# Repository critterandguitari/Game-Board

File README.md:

Game-Board
==========

A add-on board to the Video Critter HiRes.  It has buttons and a USB port for proramming the Video Critter HiRes from computer.

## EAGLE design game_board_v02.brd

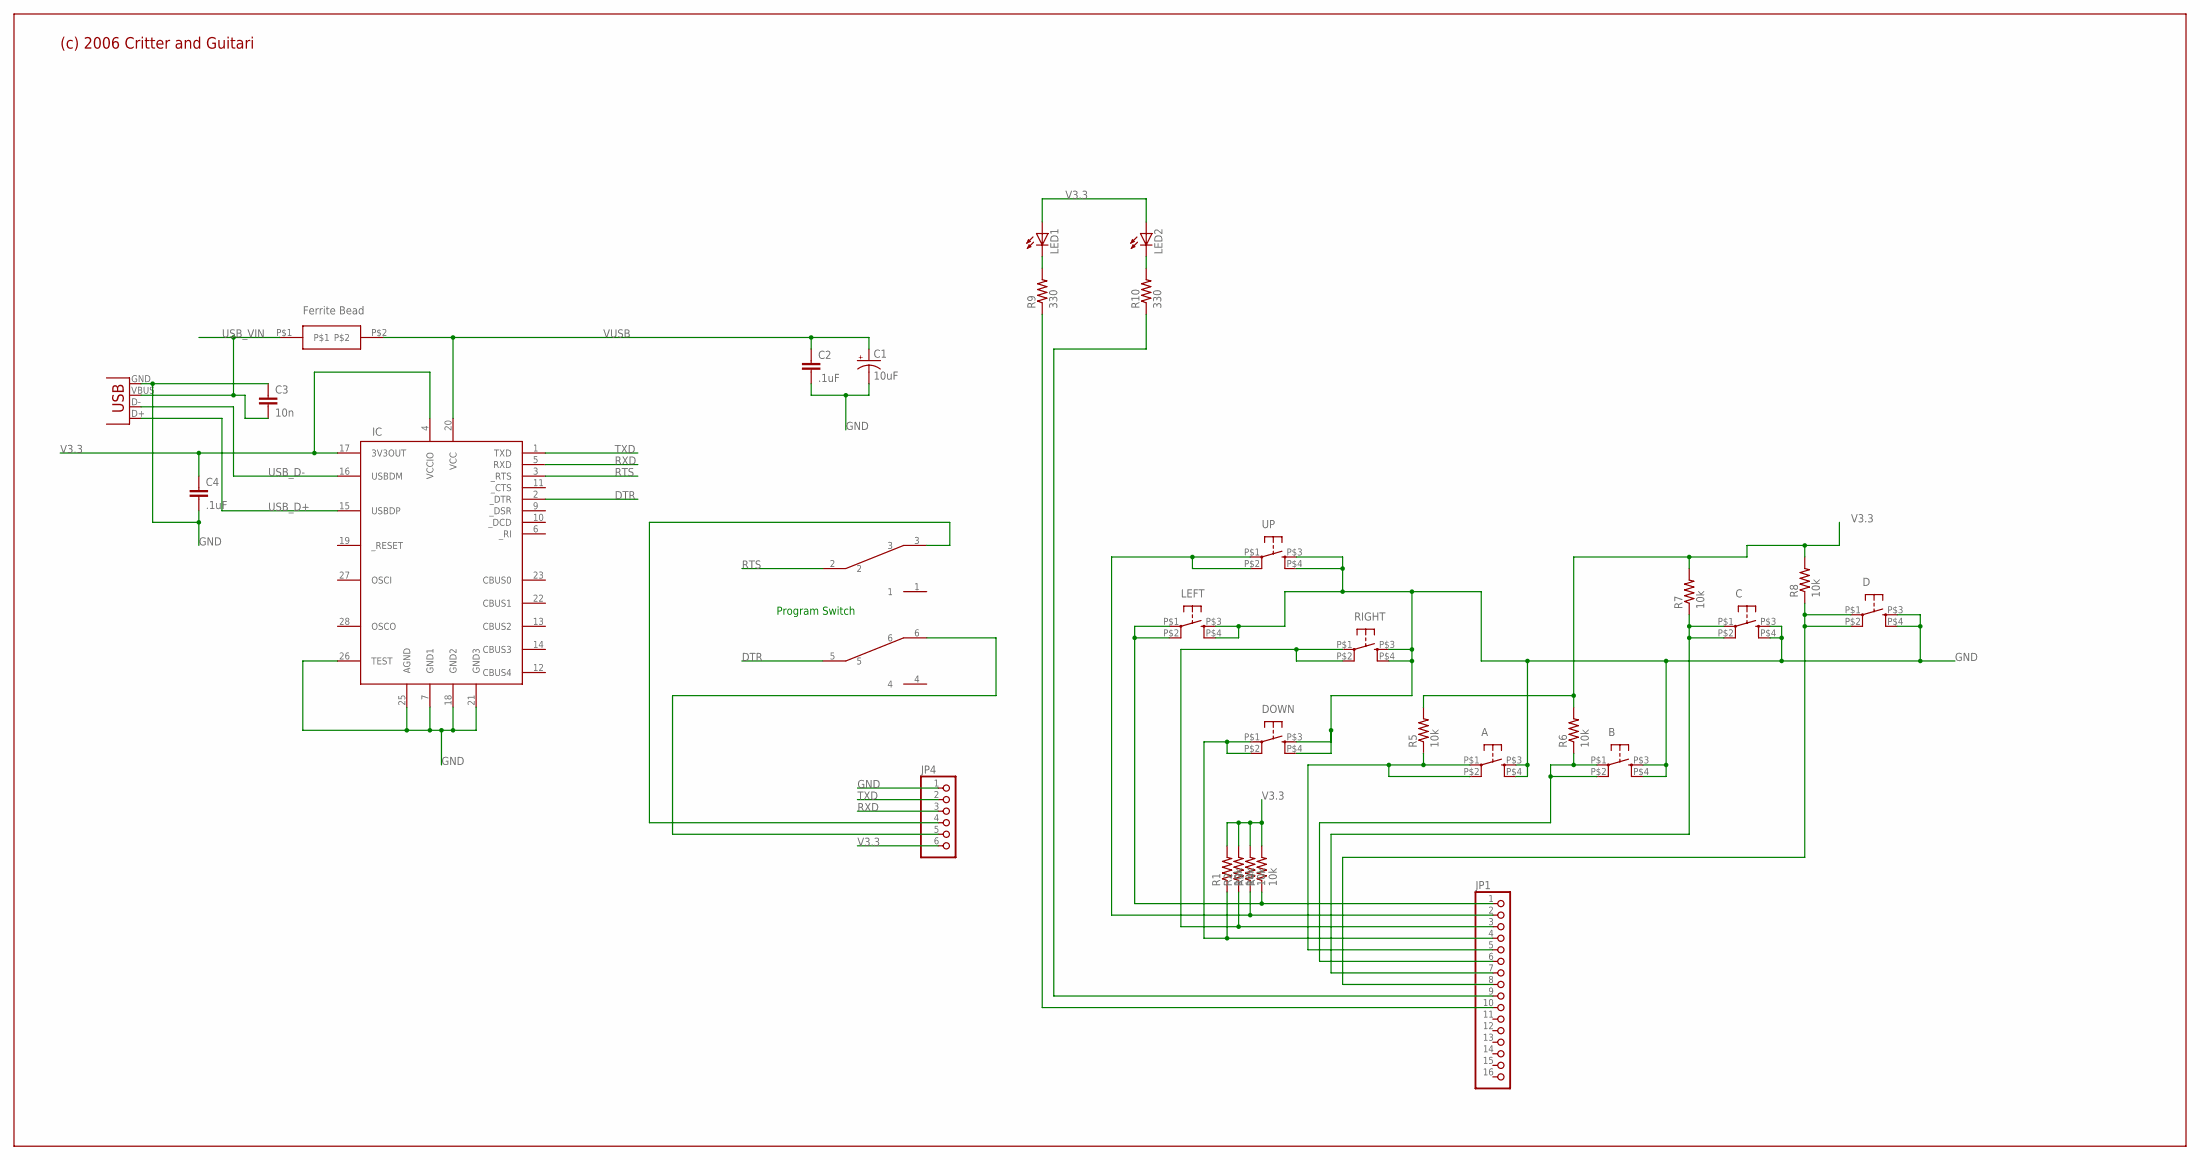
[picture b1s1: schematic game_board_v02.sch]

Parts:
A: TAC_SWITCHKSA_SEALED_TAC_SWITCH; KSA_SEALED_TAC_SWITCH
B: TAC_SWITCHKSA_SEALED_TAC_SWITCH; KSA_SEALED_TAC_SWITCH
C: TAC_SWITCHKSA_SEALED_TAC_SWITCH; KSA_SEALED_TAC_SWITCH
C1: 10uF; CPOL_1206
C2, C4: .1uF; C0603
C3: 10n; C0603
D: TAC_SWITCHKSA_SEALED_TAC_SWITCH; KSA_SEALED_TAC_SWITCH
DOWN: TAC_SWITCHKSA_SEALED_TAC_SWITCH; KSA_SEALED_TAC_SWITCH
IC: FT232RL; SSOP28DB
JP1: PINHD-1X16; 1X16
JP4: PINHD-1X6; 1X06
LED1, LED2: LED1206; CHIPLED_1206
LEFT: TAC_SWITCHKSA_SEALED_TAC_SWITCH; KSA_SEALED_TAC_SWITCH
R1, R2, R3, R4, R5, R6, R7, R8: 10k; R0603
R9, R10: 330; R0603
RIGHT: TAC_SWITCHKSA_SEALED_TAC_SWITCH; KSA_SEALED_TAC_SWITCH
U$1: FERRITE_BEAD
U$2: SWITCH_DPDT; SWITCH_DPDT_SMT
UP: TAC_SWITCHKSA_SEALED_TAC_SWITCH; KSA_SEALED_TAC_SWITCH
X2: USB-B-H

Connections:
DTR: IC.2 (_DTR), U$2.5
GND: A.P$3 (S), A.P$4 (S1), B.P$3 (S), B.P$4 (S1), C.P$3 (S), C.P$4 (S1), C1.C (-), C2.2, C3.1, C4.2, D.P$3 (S), D.P$4 (S1), DOWN.P$3 (S), DOWN.P$4 (S1), IC.7 (GND1), IC.18 (GND2), IC.21 (GND3), IC.25 (AGND), IC.26 (TEST), JP4.1, LEFT.P$3 (S), LEFT.P$4 (S1), RIGHT.P$3 (S), RIGHT.P$4 (S1), UP.P$3 (S), UP.P$4 (S1), X2.GND
unnamed: JP4.4, U$2.3
unnamed: JP4.5, U$2.6
unnamed: JP1.1, LEFT.P$1, LEFT.P$2 (P1), R4.1
unnamed: JP1.2, R3.1, UP.P$1, UP.P$2 (P1)
unnamed: JP1.3, R2.1, RIGHT.P$1, RIGHT.P$2 (P1)
unnamed: DOWN.P$1, DOWN.P$2 (P1), JP1.4, R1.1
unnamed: A.P$1, A.P$2 (P1), JP1.5, R5.1
unnamed: B.P$1, B.P$2 (P1), JP1.6, R6.1
unnamed: C.P$1, C.P$2 (P1), JP1.7, R7.1
unnamed: D.P$1, D.P$2 (P1), JP1.8, R8.1
unnamed: LED1.C, R9.2
unnamed: LED2.C, R10.2
unnamed: JP1.10, R9.1
unnamed: JP1.9, R10.1
RTS: IC.3 (_RTS), U$2.2
RXD: IC.5 (RXD), JP4.3
TXD: IC.1 (TXD), JP4.2
USB_D+: IC.15 (USBDP), X2.D+
USB_D-: IC.16 (USBDM), X2.D-
USB_VIN: C3.2, U$1.P$1, X2.VBUS
V3.3: C4.1, IC.4 (VCCIO), IC.17 (3V3OUT), JP4.6, LED1.A, LED2.A, R1.2, R2.2, R3.2, R4.2, R5.2, R6.2, R7.2, R8.2
VUSB: C1.A (+), C2.1, IC.20 (VCC), U$1.P$2

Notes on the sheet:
Ferrite Bead
(c) 2006 Critter and Guitari
Program Switch

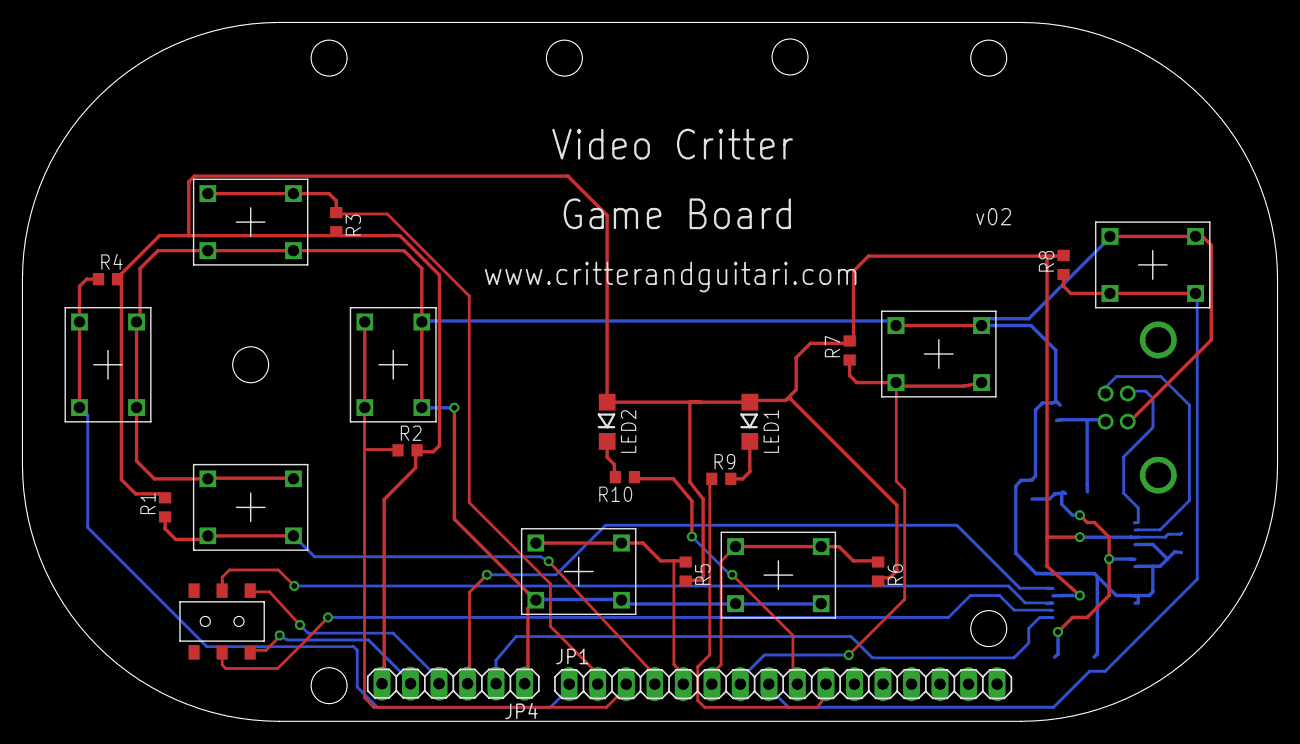
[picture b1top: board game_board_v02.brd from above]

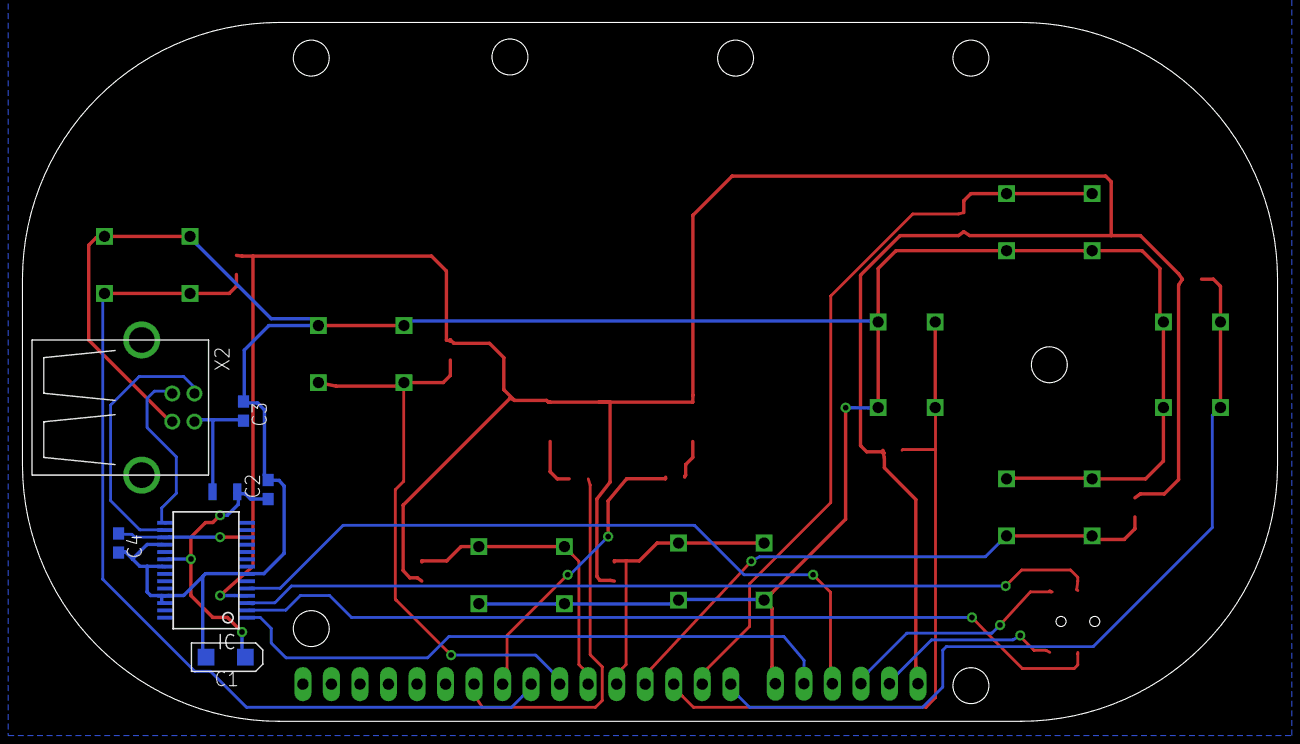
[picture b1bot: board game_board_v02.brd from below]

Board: 2 copper layers, 111.8 x 62.2 mm, 30 parts (7 on the bottom side), 24 nets.

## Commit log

2013-04-22 adding eagle files
